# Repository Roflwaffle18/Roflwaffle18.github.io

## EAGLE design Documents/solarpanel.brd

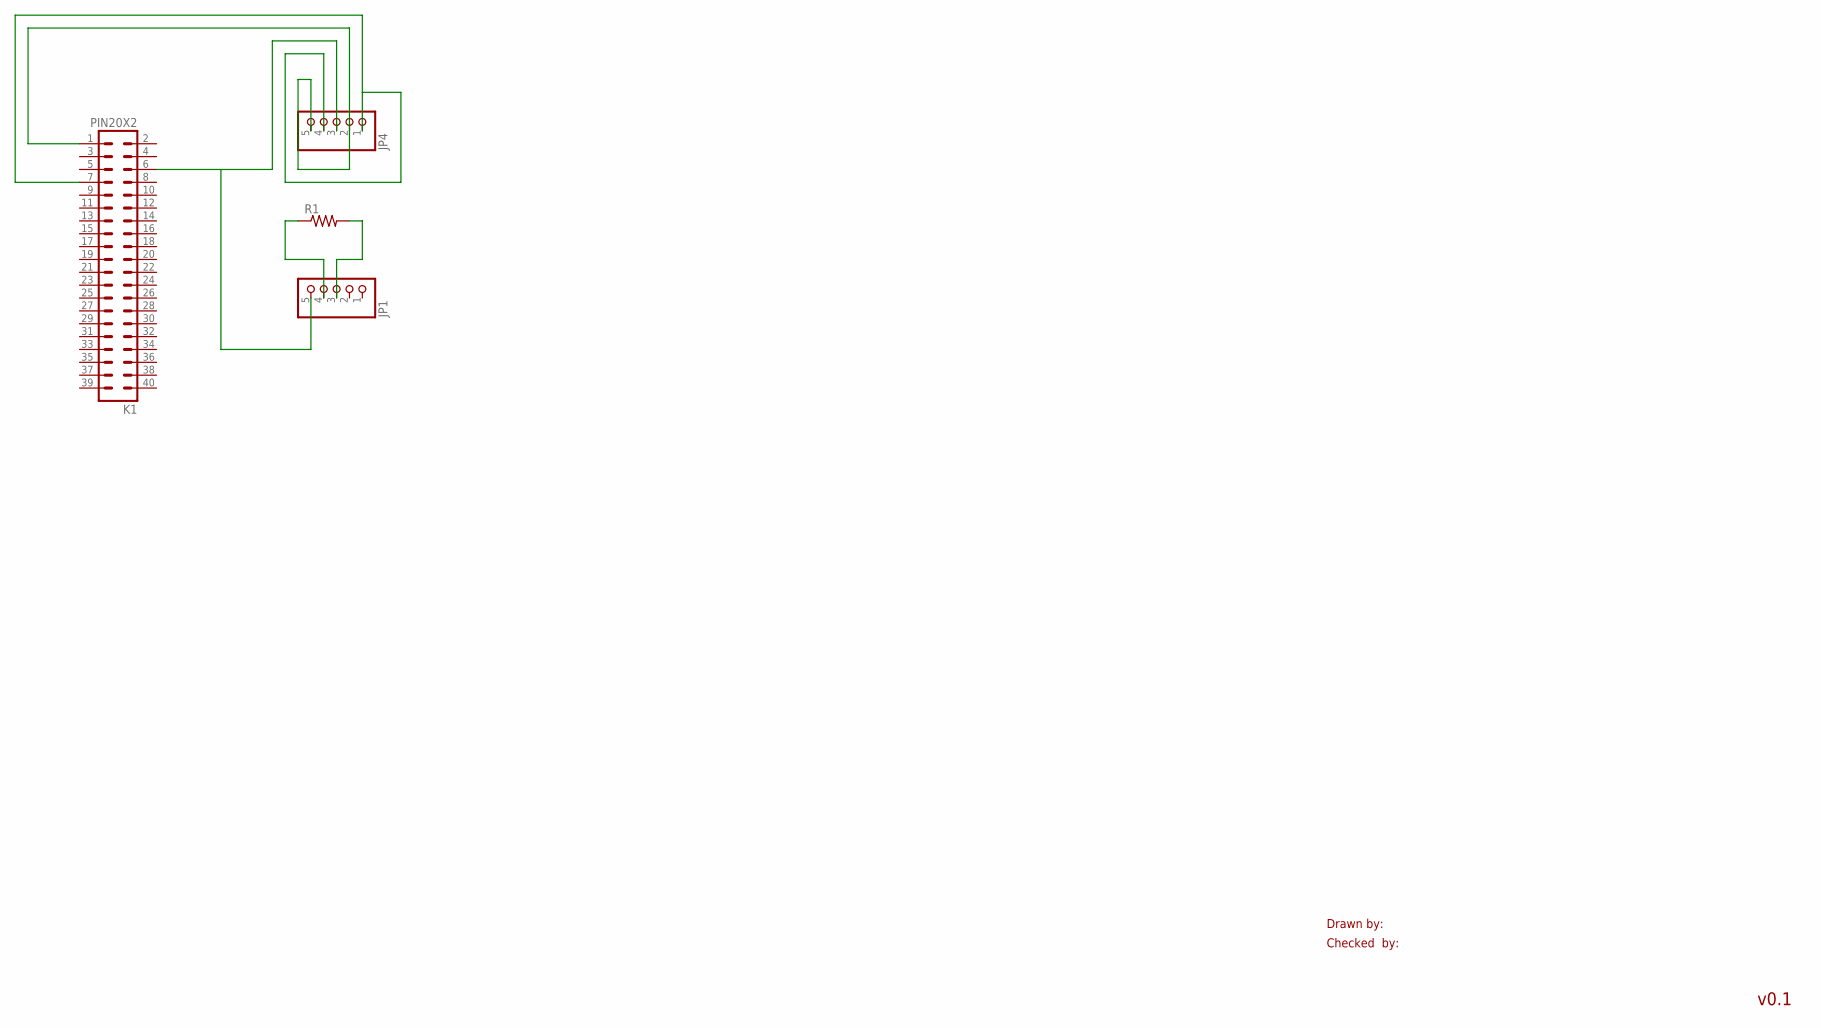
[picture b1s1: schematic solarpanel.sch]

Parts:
JP1, JP4: PINHD-1X5; 1X05
K1: PIN20X2; PIN_20X2
R1: R-US_0207/10; 0207/10

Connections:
unnamed: JP4.2, JP4.5, K1.1
unnamed: JP1.5, JP4.3, K1.6
unnamed: JP4.1, JP4.4, K1.7
unnamed: JP1.4, R1.1
unnamed: JP1.3, R1.2

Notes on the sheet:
Drawn by:
Checked by:
v0.1

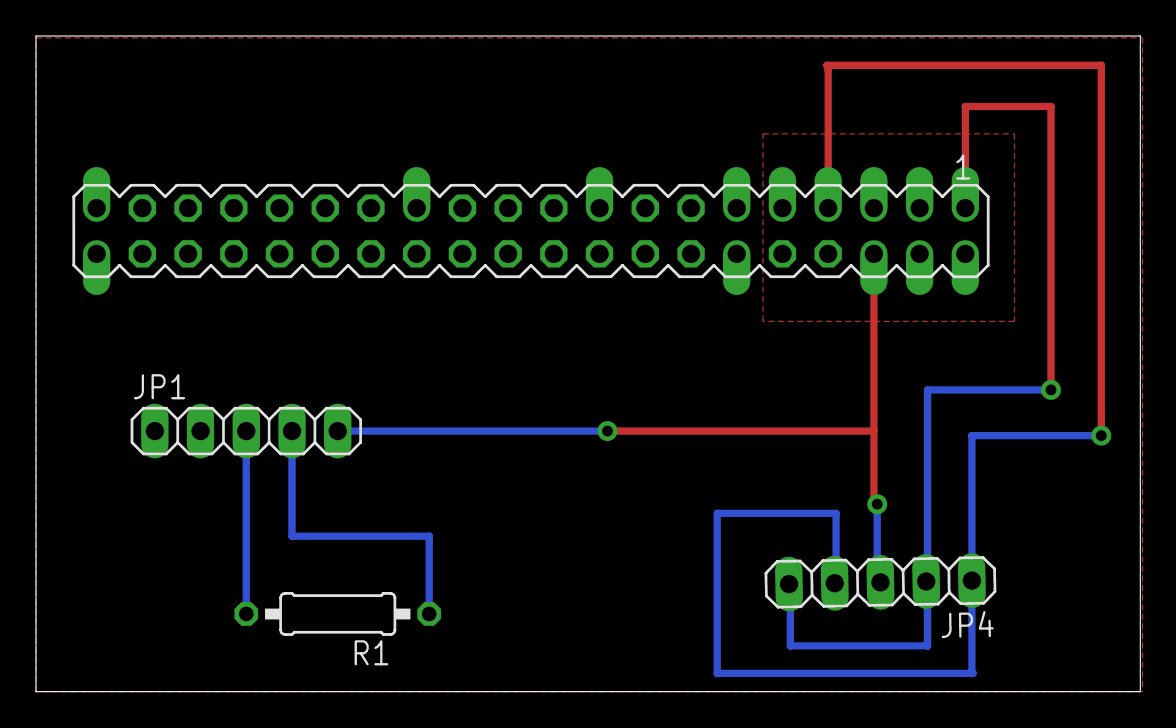
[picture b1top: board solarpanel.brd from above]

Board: 2 copper layers, 61.4 x 36.4 mm, 4 parts (0 on the bottom side), 5 nets.

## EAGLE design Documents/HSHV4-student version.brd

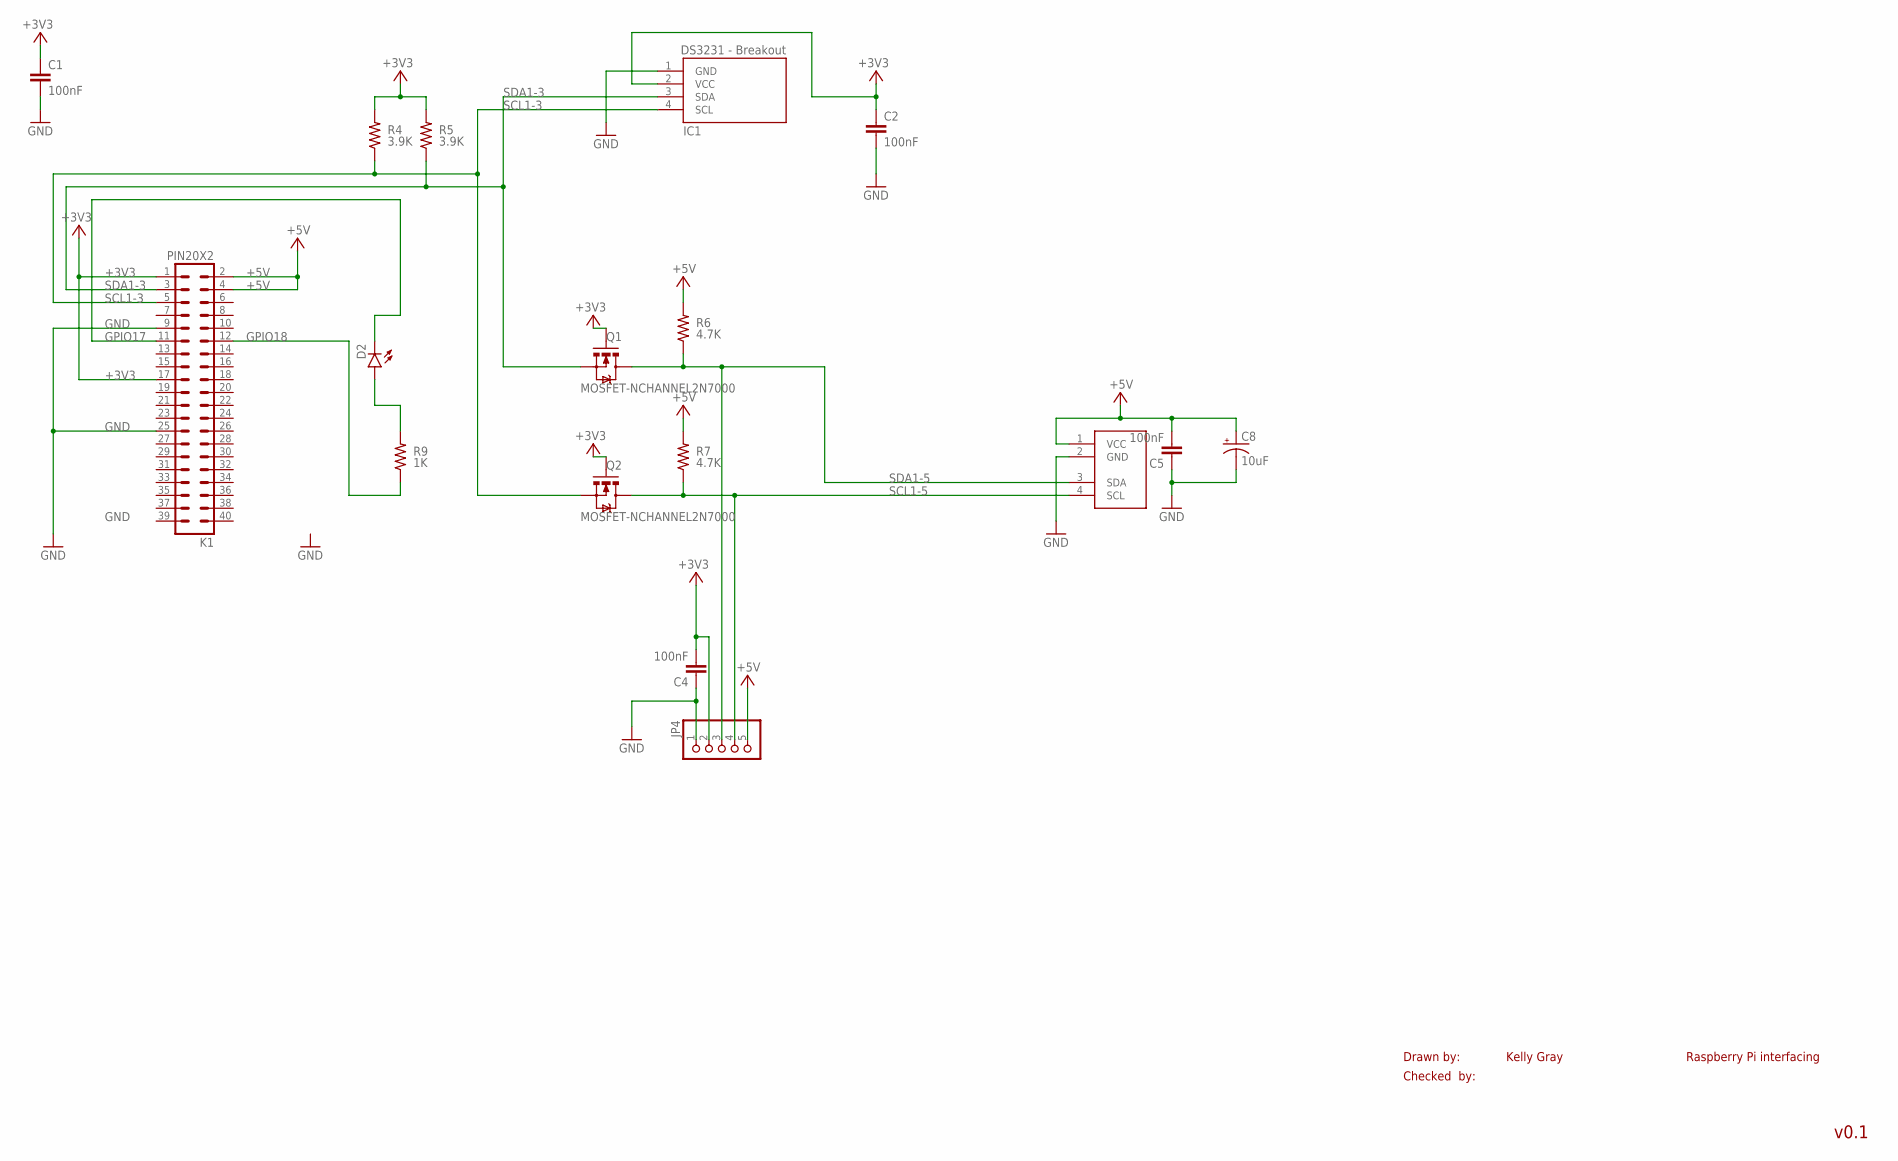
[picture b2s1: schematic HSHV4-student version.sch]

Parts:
C1, C2, C4, C5: 100nF; CAP-PTH-SMALL-KIT
C8: 10uF; CPOL-RADIAL-10UF-25V
D2: LED-3MM-NO_SILK; LED3MM-NS
IC1: DS3231; 8PTH
JP4: PINHD-1X5; 1X05
K1: PIN20X2; PIN_20X2
Q1, Q2: MOSFET-NCHANNEL2N7000; TO-92
R4, R5: 3.9K; AXIAL-0.3; TOLERANCE 5%
R6, R7: 4.7K; AXIAL-0.3; TOLERANCE 5%
R9: 1K; AXIAL-0.3; TOLERANCE 5%
U$1: PCF8591; 1X04

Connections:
+3V3: C1.1, C2.1, C4.2, IC1.2 (VCC), JP4.2, K1.1, K1.17, Q1.2 (G), Q2.2 (G), R4.P$2 (2), R5.P$2 (2)
+5V: C5.2, C8.1 (+), JP4.5, K1.2, K1.4, R6.P$2 (2), R7.P$2 (2), U$1.1 (VCC)
GND: C1.2, C2.2, C4.1, C5.1, C8.2 (-), IC1.1 (GND), JP4.1, K1.9, K1.25, U$1.2 (GND)
GPIO17: D2.K (C), K1.11
GPIO18: K1.12, R9.P$1 (1)
unnamed: D2.A, R9.P$2 (2)
SCL1-3: IC1.4 (SCL), K1.5, Q2.1 (S), R4.P$1 (1)
SCL1-5: JP4.4, Q2.3 (D), R7.P$1 (1), U$1.4 (SCL)
SDA1-3: IC1.3 (SDA), K1.3, Q1.1 (S), R5.P$1 (1)
SDA1-5: JP4.3, Q1.3 (D), R6.P$1 (1), U$1.3 (SDA)

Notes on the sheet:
Drawn by:
Checked by:
Kelly Gray
v0.1
Raspberry Pi interfacing

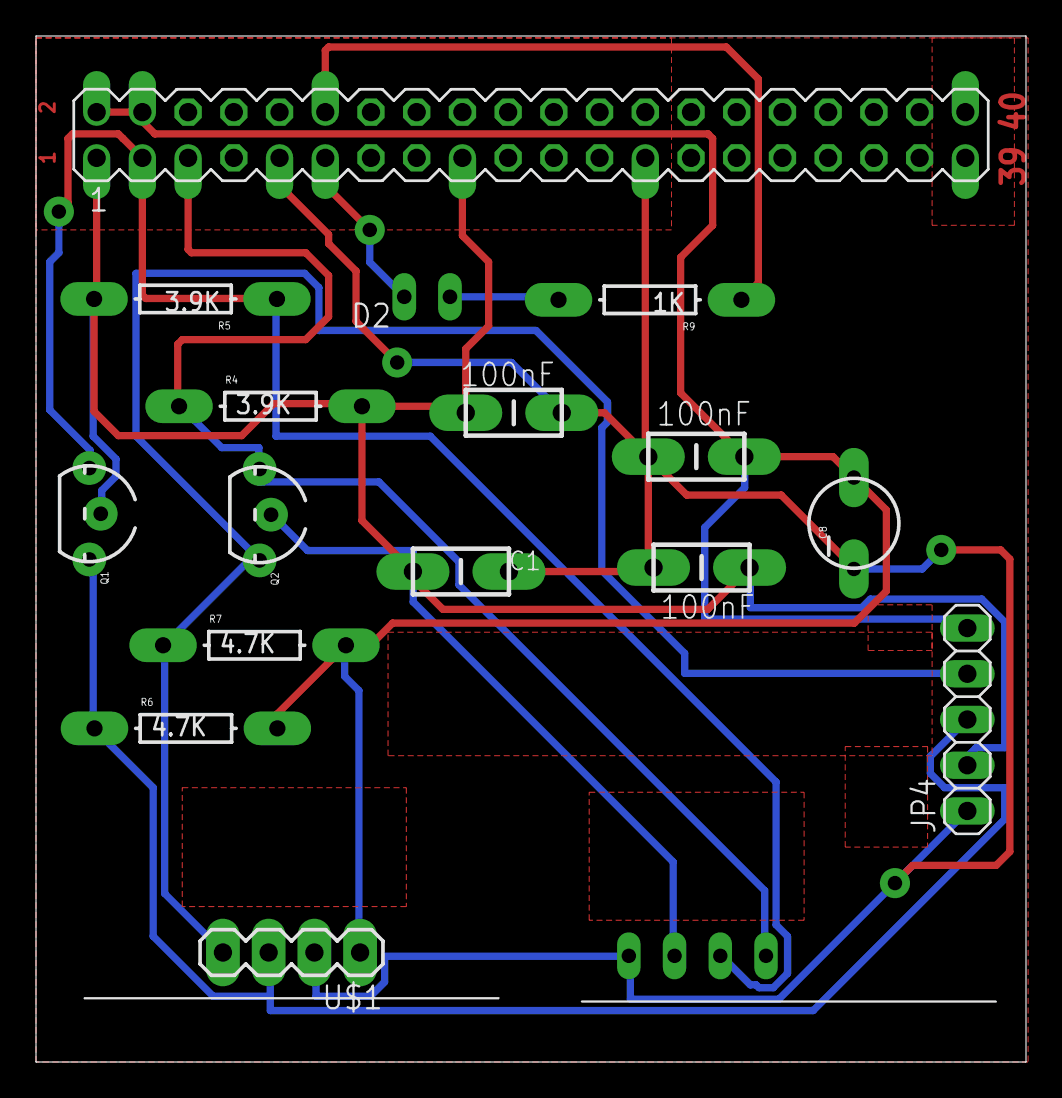
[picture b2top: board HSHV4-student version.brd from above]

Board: 2 copper layers, 55.0 x 57.0 mm, 17 parts (0 on the bottom side), 10 nets.

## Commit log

2016-09-06 :octocat: Added .gitattributes & .gitignore files
2016-09-06 Salvatore's Repository
2016-09-20 Added the html for site
2016-09-20 Added web templates
    added the templates for the html
2016-09-27 Updated site
2016-09-27 Changed more stuff
2016-09-27 test again
2016-09-27 Completed Week 1 and Week 4 Sections
2016-10-04 Oct. 4th Update
    - Implemented Project Schedule download
    - Implemented Week 5
2016-10-04 Oct. 4th Update (2)
    - Bug Fix for week 3 download
    - Implemented Week 5 project update download
2016-10-11 Oct. 11 Update
    - Added week 6
2016-10-11 Oct. 11 Update (2)
2016-10-14 Oct. 14 Update
2016-11-01 Update Nov. 1
    Forgot to update it in a little bit
2016-11-01 Update Nov. 1 - 2
    Added Week 9 and polished up the site
2016-11-01 Update Nov. 1 - 3
    Another fix
2016-11-08 Update Nov. 8, 2016
    - Added week 10 blog post
2016-11-15 Update - Nov. 8, 2016
    - Added week 11 and week 11 folder
2016-11-15 Update - Nov. 15, 2016 - 2
    - Added the picture permissions for the open house picture as I forgot
    to do that
2016-11-15 Update - Nov. 15, 2016 - 3
    Some formatting corrections
2016-11-15 Update - Nov. 15, 2016 - 4
    - Added file to download for progress report week 11
2016-11-15 Update - Nov. 15, 2016 - 5
    - Financial update has be corrected
2016-11-22 Update - Nov. 22
    - Added week 12 blog post
2016-12-06 Update Dec. 6, 2016
    - Added a build instructions link (still in progress)
    - Mostly done build instructions
2016-12-06 Update Dec. 6, 2016 - 2
    Completed the project build instructions
2016-12-07 UPDATE IMPORTANT
    Steve asked me today where my build log was and I said it was on my
    site, turns out I forgot to add a link to it soooooo I fixed it, it is
    in the quick links menu now

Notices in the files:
parts and their libraries:
SparkFun-Resistors: Licensing: Creative Commons ShareAlike 4.0 International - https://creativecommons.org/licenses/by-sa/4.0
